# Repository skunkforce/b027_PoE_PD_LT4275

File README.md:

# edgy_board number b027
This design is part of the [edgy board project](https://github.com/skunkforce/edgy_boards). It provides a PoE Power Device capable of 100W. 

# getting started
This repository uses submodules. After cloning use the command 

```$ git submodule update --init --recursive```

to pull the submodules before opening the project with kicad. 

# Tests
Tests can be found in [TESTS.md](TESTS.md)

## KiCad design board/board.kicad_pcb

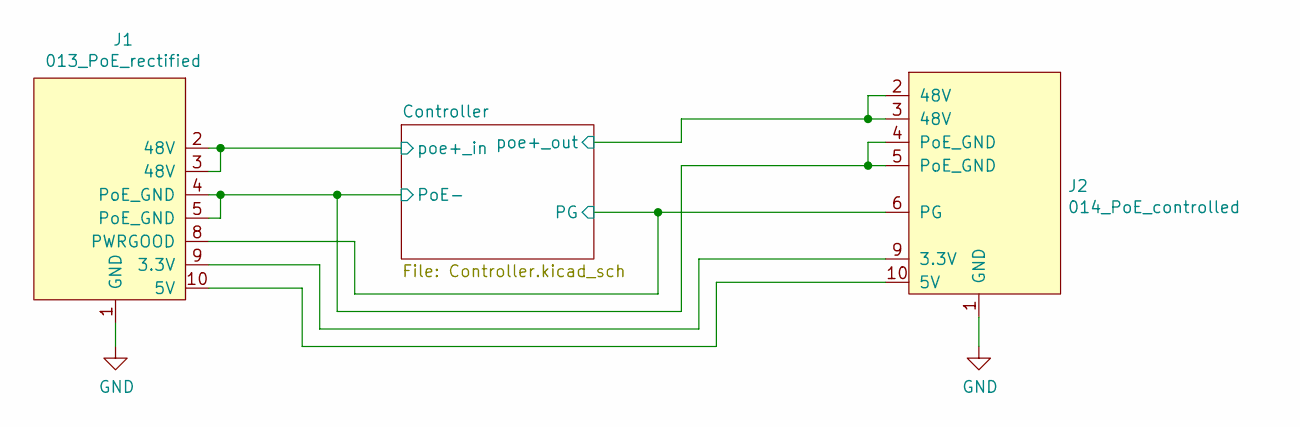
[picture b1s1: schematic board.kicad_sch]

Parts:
J1: 013_PoE_rectified; on_edge_2x05_device
J2: 014_PoE_controlled; on_edge_2x05_host

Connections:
/Controller/PG: J1.8 (PWRGOOD), J2.6 (PG); also elsewhere on the board
/Controller/PoE-: J1.4 (PoE_GND), J1.5 (PoE_GND), J2.4 (PoE_GND), J2.5 (PoE_GND); also elsewhere on the board
/Controller/poe+_in: J1.2 (48V), J1.3 (48V); also elsewhere on the board
/Controller/poe+_out: J2.2 (48V), J2.3 (48V); also elsewhere on the board
GND: J1.1 (GND), J2.1 (GND)
unnamed: J1.9 (3.3V), J2.9 (3.3V)
unnamed: J1.10 (5V), J2.10 (5V)

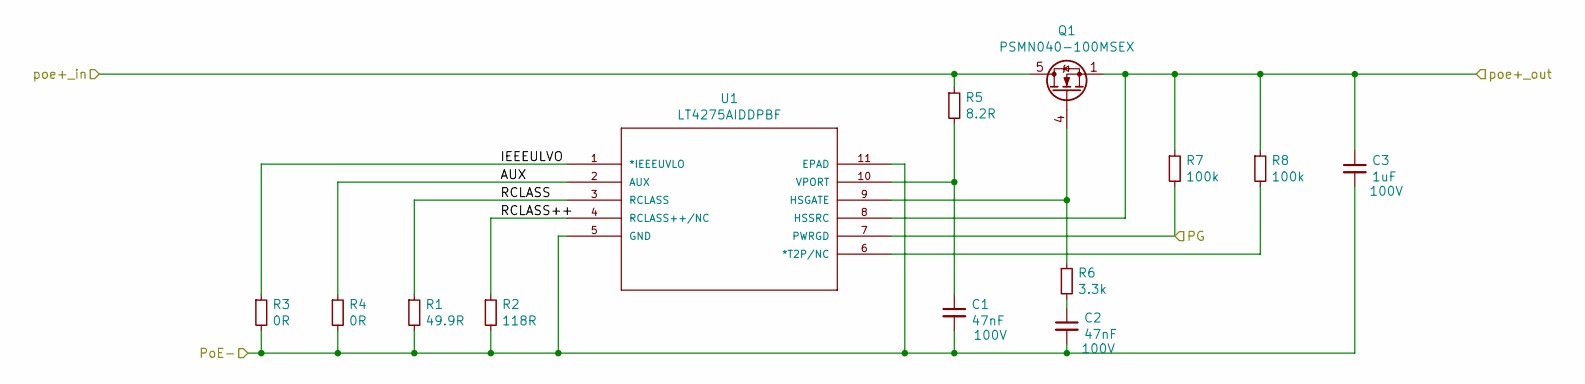
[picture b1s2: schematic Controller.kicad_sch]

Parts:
C1, C2: 47nF; C_0603_1608Metric; Voltage 100V
C3: 1uF; C_1206_3216Metric; Voltage 100V
Q1: PSMN040-100MSEX; LFPAK33
R1: 49.9R; R_0603_1608Metric
R2: 118R; R_0603_1608Metric
R3, R4: 0R; R_0603_1608Metric
R5: 8.2R; R_0603_1608Metric
R6: 3.3k; R_0603_1608Metric
R7, R8: 100k; R_0603_1608Metric
U1: LT4275AIDDPBF; DFN-10-1EP_3x3mm_P0.5mm_EP1.65x2.38mm_ThermalVias; MANUFACTURER_PART_NUMBER lt4275aidd#pbf

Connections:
/Controller/AUX: R4.1, U1.2 (AUX)
/Controller/IEEEULVO: R3.1, U1.1 (*IEEEUVLO)
/Controller/PG: R7.2, U1.7 (PWRGD); also elsewhere on the board
/Controller/PoE-: C1.2, C2.2, C3.2, R1.2, R2.2, R3.2, R4.2, U1.5 (GND), U1.11 (EPAD); also elsewhere on the board
/Controller/RCLASS: R1.1, U1.3 (RCLASS)
/Controller/RCLASS++: R2.1, U1.4 (RCLASS++/NC)
/Controller/poe+_in: Q1.5 (D), R5.1; also elsewhere on the board
/Controller/poe+_out: C3.1, Q1.1 (S), Q1.2 (S), Q1.3 (S), R7.1, R8.1, U1.8 (HSSRC); also elsewhere on the board
unnamed: C1.1, R5.2, U1.10 (VPORT)
unnamed: C2.1, R6.2
unnamed: Q1.4 (G), R6.1, U1.9 (HSGATE)
unnamed: R8.2, U1.6 (*T2P/NC)

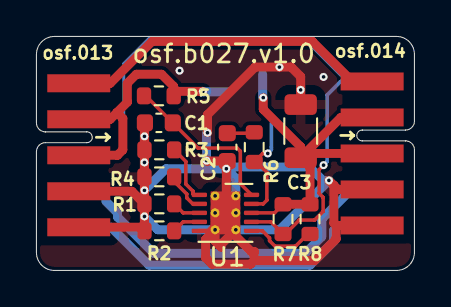
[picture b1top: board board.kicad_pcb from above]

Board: 2 copper layers, 21.0 x 13.0 mm, 15 parts (1 on the bottom side), 15 nets.

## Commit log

2023-02-24 improved description
2023-02-25 imported legacy version
2023-03-01 added schematic and footprint from legacy project
2023-03-01 changed PSMN5R2 footprint from LFPAK33 to LFPAK56
    The PSMN5R2 is not available in LFPAK33.
2023-03-05 changed fp Q1 to back
2023-03-05 Moved Q1 from front to back
    Q1 from front to back and keeped the size of pcb
2023-05-13 updated connectors
2023-05-14 added power doo cinnection upstream
